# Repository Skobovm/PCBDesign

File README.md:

# PCBDesign
Re-learning how to use EAGLE, and various other circuits

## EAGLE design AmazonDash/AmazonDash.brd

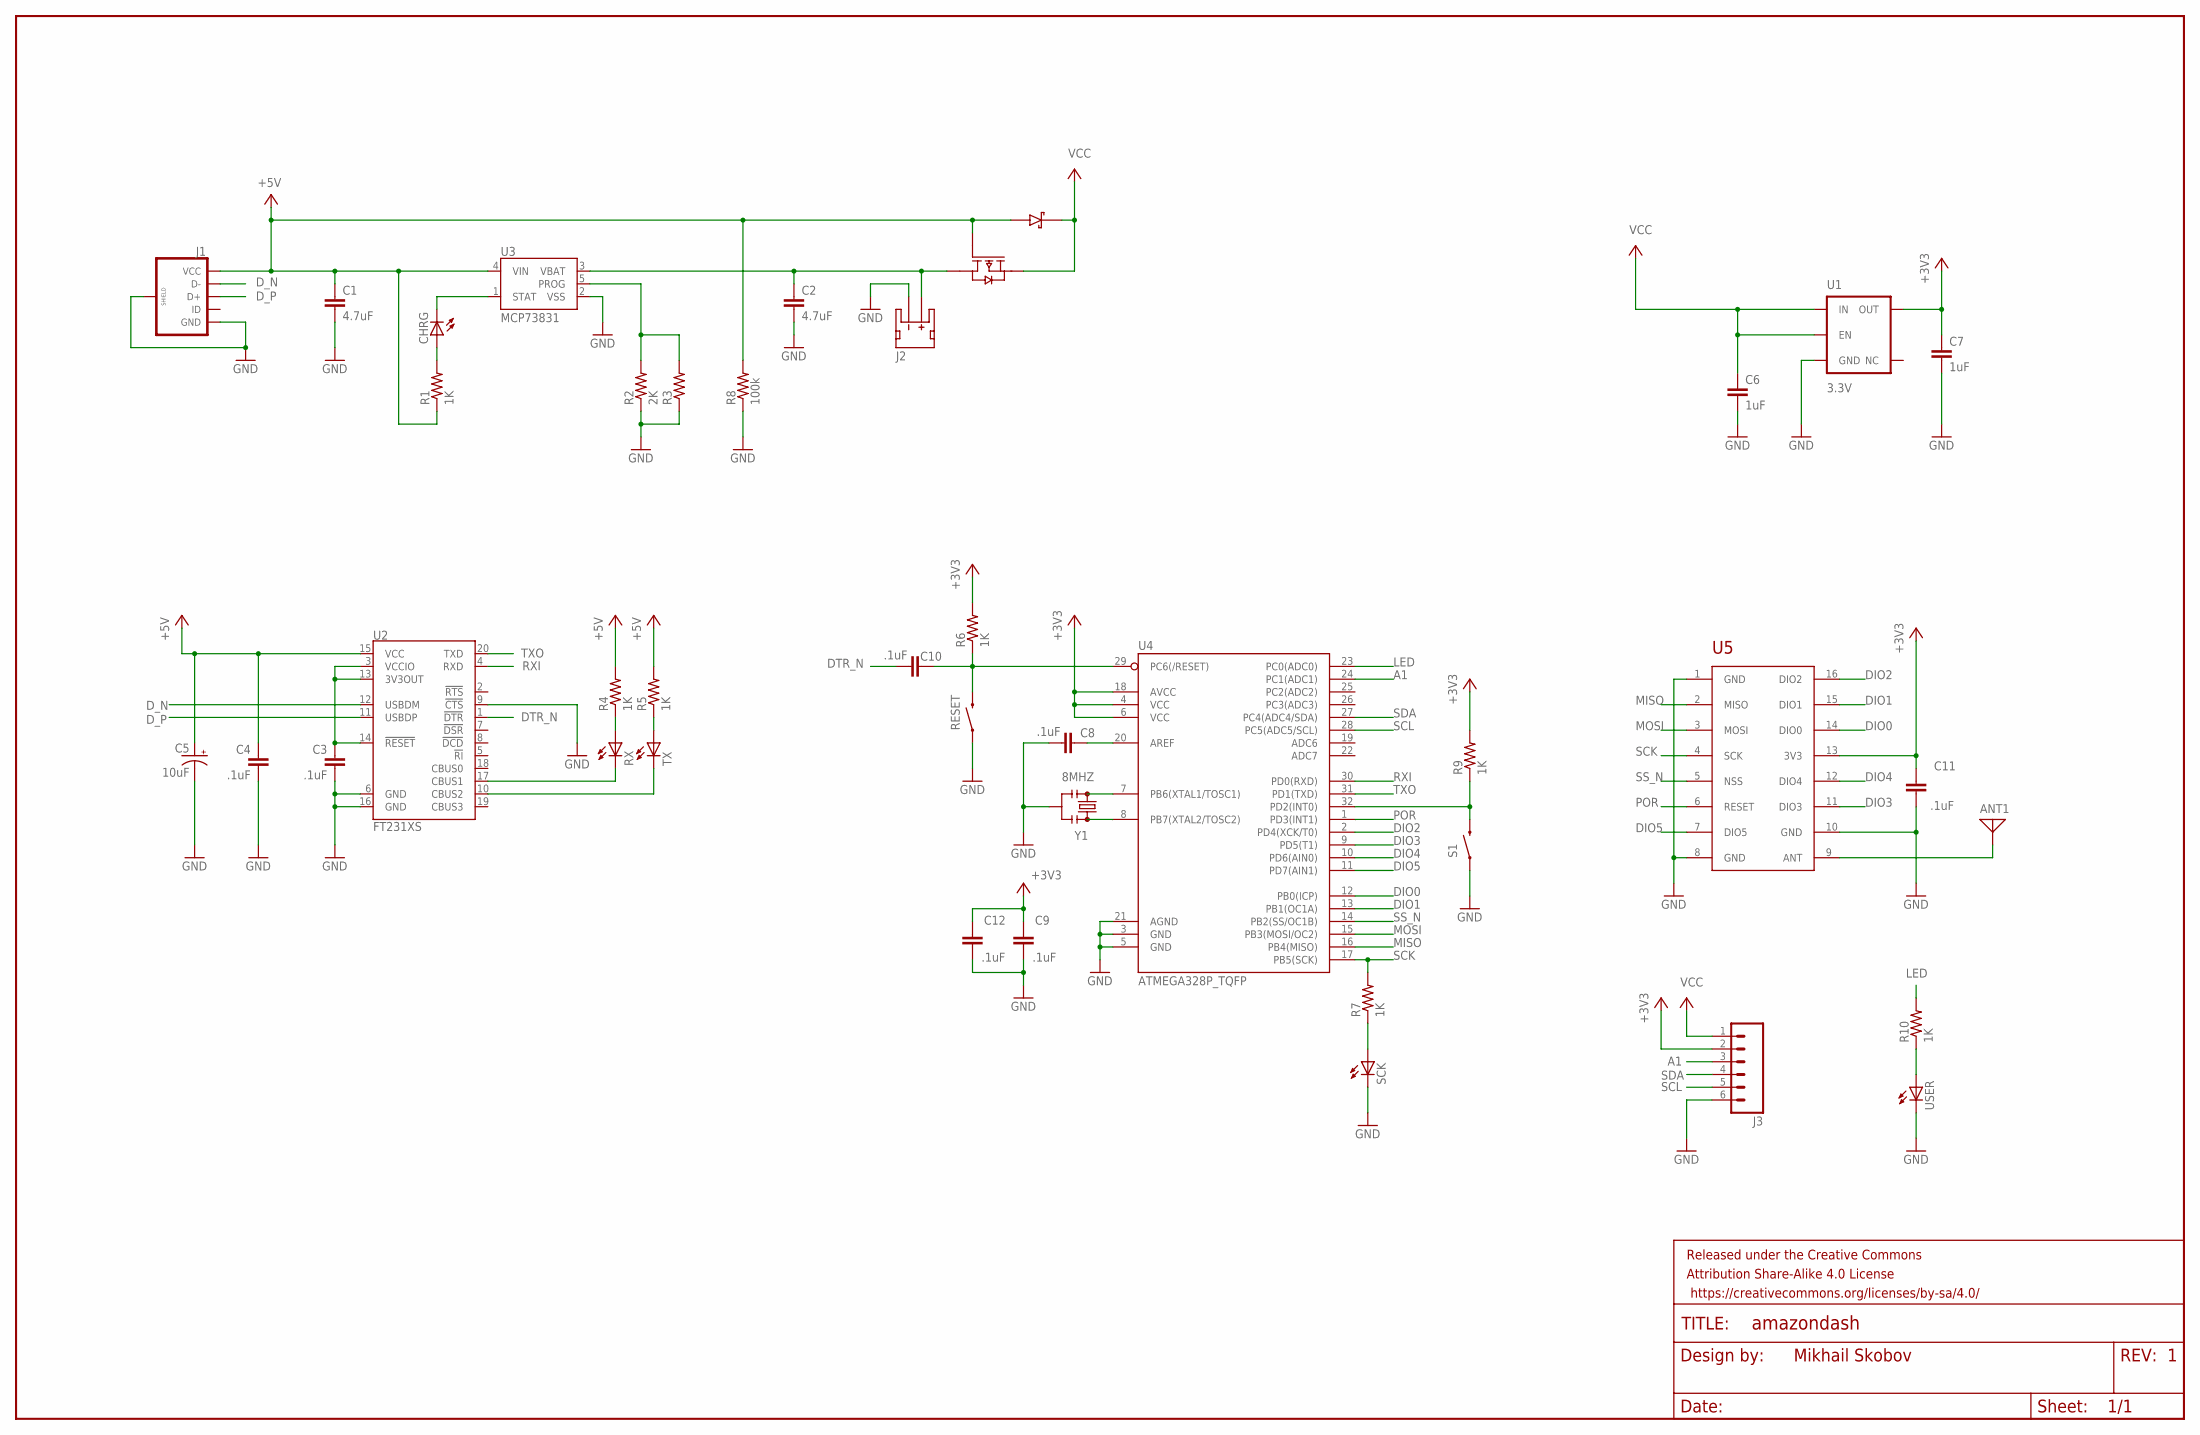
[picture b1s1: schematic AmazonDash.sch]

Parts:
ANT1: ANTENNA; PAD-01
C1, C2: 4.7uF; C0805
C3, C4, C8, C9, C10, C11, C12: .1uF; C0805
C5: 10uF; EIA3216
C6, C7: 1uF; C0805
CHRG: LEDCHIPLED_0805; CHIPLED_0805
FRAME2: FRAME-LEDGER; CREATIVE_COMMONS
J1: USB_MICROB_PLUGCONN-11752; USB-B-MICRO-SMD_V03
J2: JST_2MM_MALE; JST-2-SMD
J3: M06LOCK; 1X06_LOCK
R1, R4, R5, R6, R7, R9, R10: 1K; R0805
R2: 2K; R0805
R3: R-US_R0805; R0805
R8: 100k; R0805
RESET: SWITCH-MOMENTARY-2SMD; TACTILE-SWITCH-SMD
RX: LEDCHIPLED_0805; CHIPLED_0805
S1: SWITCH-MOMENTARY-2SMD; TACTILE-SWITCH-SMD
SCK: LEDCHIPLED_0805; CHIPLED_0805
TX: LEDCHIPLED_0805; CHIPLED_0805
U1: 3.3V; SOT23-5
U2: FT231XS; SSOP20_L
U3: MCP73831; SOT23-5
U4: ATMEGA328P_TQFP; TQFP32-08
U5: RFM69HCW; RFM69
U6: FDC6392S; SSOT-6
USER: LEDCHIPLED_0805; CHIPLED_0805
Y1: 8MHZ; RESONATOR-SMD

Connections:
+3V3: C7.1, C9.2, C11.2, C12.2, J3.2, R6.2, R9.2, U1.5 (OUT), U4.4 (VCC), U4.6 (VCC), U4.18 (AVCC), U5.13 (3V3)
+5V: C1.1, C4.1, C5.A (+), J1.VBUS (VCC), R1.1, R4.2, R5.2, R8.2, U2.15 (VCC), U3.4 (VIN), U6.1 (A), U6.3 (G)
A1: J3.3, U4.24 (PC1(ADC1))
DIO0: U4.12 (PB0(ICP)), U5.14 (DIO0)
DIO1: U4.13 (PB1(OC1A)), U5.15 (DIO1)
DIO2: U4.2 (PD4(XCK/T0)), U5.16 (DIO2)
DIO3: U4.9 (PD5(T1)), U5.11 (DIO3)
DIO4: U4.10 (PD6(AIN0)), U5.12 (DIO4)
DIO5: U4.11 (PD7(AIN1)), U5.7 (DIO5)
DTR_N: C10.1, U2.1 (!DTR)
D_N: J1.D-, U2.12 (USBDM)
D_P: J1.D+, U2.11 (USBDP)
GND: C1.2, C2.2, C3.2, C4.2, C5.C (-), C6.2, C7.2, C8.1, C9.1, C11.1, C12.1, J1.GND, J1.SHIELD1 (SHIELD), J1.SHIELD2 (SHIELD), J1.SHIELD3 (SHIELD), J2.1 (-), J3.6, R2.1, R3.1, R8.1, RESET.1, S1.1, SCK.C, U1.2 (GND), U2.6 (GND), U2.9 (!CTS), U2.16 (GND), U3.2 (VSS), U4.3 (GND), U4.5 (GND), U4.21 (AGND), U5.1 (GND), U5.8 (GND), U5.10 (GND), USER.C, Y1.2
LED: R10.2, U4.23 (PC0(ADC0))
MISO: U4.16 (PB4(MISO)), U5.2 (MISO)
MOSI: U4.15 (PB3(MOSI/OC2)), U5.3 (MOSI)
unnamed: RX.C, U2.17 (CBUS1)
unnamed: CHRG.C, U3.1 (STAT)
unnamed: CHRG.A, R1.2
unnamed: R4.1, RX.A
unnamed: R5.1, TX.A
unnamed: R2.2, R3.2, U3.5 (PROG)
unnamed: TX.C, U2.10 (CBUS2)
unnamed: C3.1, U2.3 (VCCIO), U2.13 (3V3OUT), U2.14 (!RESET)
unnamed: R9.1, S1.3 (2), U4.32 (PD2(INT0))
unnamed: R10.1, USER.A
unnamed: R7.1, SCK.A
unnamed: C10.2, R6.1, RESET.3 (2), U4.29 (PC6(/RESET))
unnamed: C8.2, U4.20 (AREF)
unnamed: U4.7 (PB6(XTAL1/TOSC1)), Y1.1
unnamed: U4.8 (PB7(XTAL2/TOSC2)), Y1.3
unnamed: ANT1.1, U5.9 (ANT)
POR: U4.1 (PD3(INT1)), U5.6 (RESET)
RXI: U2.4 (RXD), U4.30 (PD0(RXD))
SCK: R7.2, U4.17 (PB5(SCK)), U5.4 (SCK)
SCL: J3.5, U4.28 (PC5(ADC5/SCL))
SDA: J3.4, U4.27 (PC4(ADC4/SDA))
SS_N: U4.14 (PB2(SS/OC1B)), U5.5 (NSS)
TXO: U2.20 (TXD), U4.31 (PD1(TXD))
VBAT: C2.1, J2.2 (+), U3.3 (VBAT), U6.4 (S)
VCC: C6.1, J3.1, U1.1 (IN), U1.3 (EN), U6.2 (D), U6.6 (C)

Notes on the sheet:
Mikhail Skobov

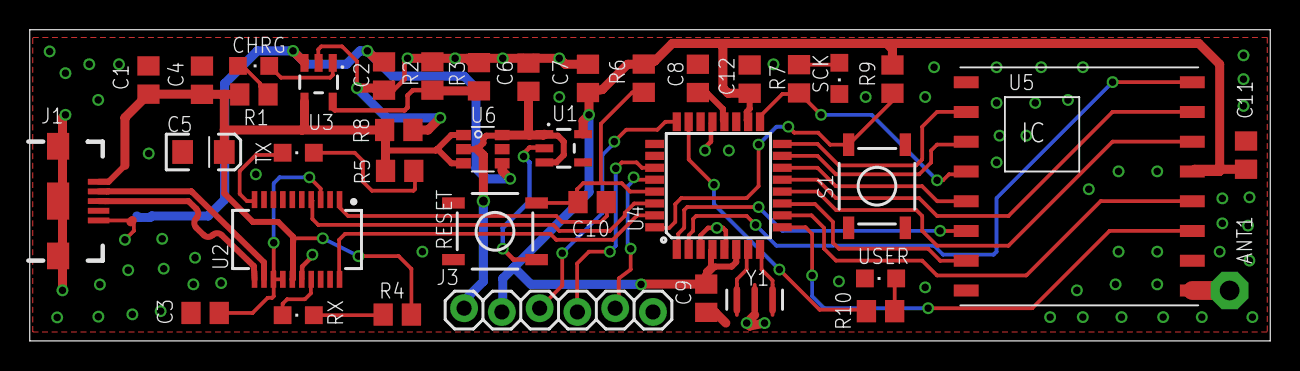
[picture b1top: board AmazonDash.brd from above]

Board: 2 copper layers, 83.4 x 20.9 mm, 41 parts (1 on the bottom side), 41 nets.

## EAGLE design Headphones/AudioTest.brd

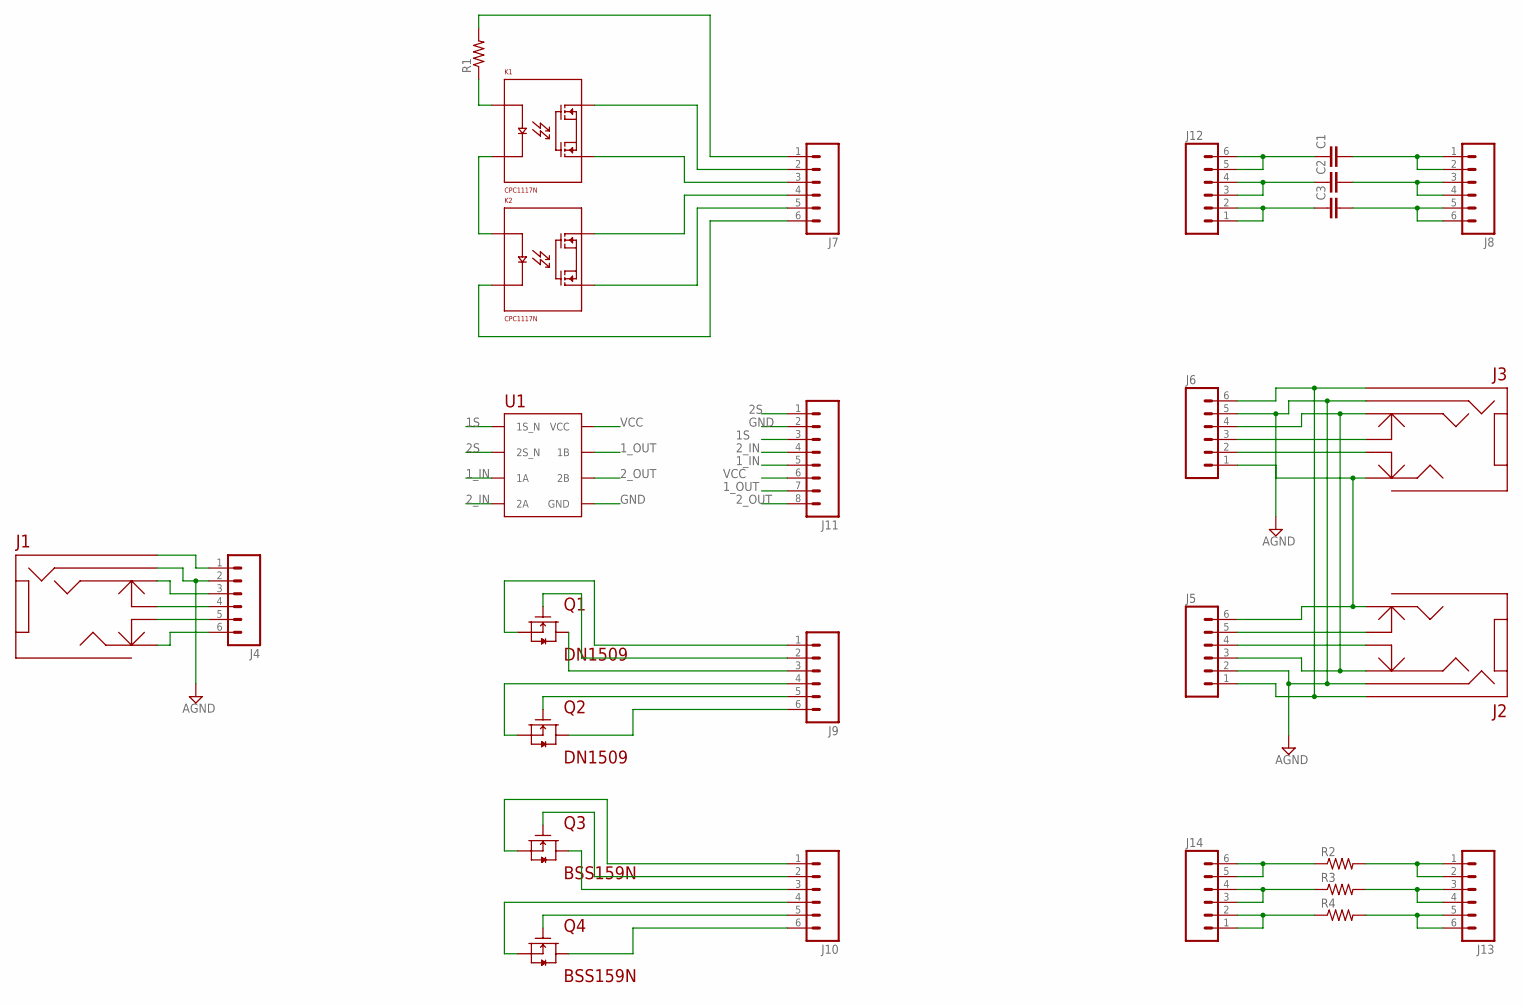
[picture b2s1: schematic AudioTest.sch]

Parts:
C1, C2, C3: C-EUC1210; C1210
J1, J2, J3: SJ-43516; SJ-43516-SMT
J4, J5, J6, J7, J8, J9, J10, J12, J13, J14: M06LOCK; 1X06_LOCK
J11: M08LOCK; 1X08_LOCK
K1, K2: CPC1117N; 4-SOP
Q1, Q2: DN1509; SOT-23-5
Q3, Q4: BSS159N; SOT-23-3
R1: R-US_R0805; R0805
R2, R3, R4: R-US_M0805; M0805
U1: FSA553; 9-UFBGA-NSMD

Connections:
1S: J11.3, U1.C1 (1S_N)
1_IN: J11.5, U1.A1 (1A)
1_L: J1.2 (LEFT), J4.6
1_L_SW: J1.5 (LEFT_NC), J4.5
1_M: J1.1 (MIC), J4.1
1_OUT: J11.7, U1.A3 (1B)
1_R: J1.3 (RIGHT), J4.3
1_R_SW: J1.6 (RIGHT_NC), J4.4
2S: J11.1, U1.C3 (2S_N)
2_IN: J11.4, U1.B1 (2A)
2_L: J2.2 (LEFT), J3.2 (LEFT), J5.6, J6.1
2_L_SW: J2.5 (LEFT_NC), J5.5
2_M: J2.1 (MIC), J3.1 (MIC), J5.1, J6.6
2_OUT: J11.8, U1.B3 (2B)
2_R: J2.3 (RIGHT), J3.3 (RIGHT), J5.3, J6.4
2_R_SW: J2.6 (RIGHT_NC), J5.4
3_SW_L: J3.5 (LEFT_NC), J6.2
3_SW_R: J3.6 (RIGHT_NC), J6.3
AGND: J1.4 (GND), J2.4 (GND), J3.4 (GND), J4.2, J5.2, J6.5
D1: J9.3, Q1.2 (D)
D2: J9.6, Q2.2 (D)
D3: J10.3, Q3.3 (D)
D4: J10.6, Q4.3 (D)
G1: J9.2, Q1.5 (G)
G2: J9.5, Q2.5 (G)
G3: J10.2, Q3.1 (G)
G4: J10.5, Q4.1 (G)
GND: J11.2, U1.C2 (GND)
unnamed: C3.1, J12.1, J12.2
unnamed: C3.2, J8.5, J8.6
unnamed: K1.1 (A), R1.1
unnamed: K1.2 (C), K2.1 (A)
unnamed: C2.2, J8.3, J8.4
unnamed: C1.2, J8.1, J8.2
unnamed: C1.1, J12.5, J12.6
unnamed: C2.1, J12.3, J12.4
unnamed: J14.1, J14.2, R4.1
unnamed: J13.5, J13.6, R4.2
unnamed: J13.3, J13.4, R3.2
unnamed: J13.1, J13.2, R2.2
unnamed: J14.5, J14.6, R2.1
unnamed: J14.3, J14.4, R3.1
R_GND: J7.6, K2.2 (C)
R_IN1: J7.2, K1.4 (LOAD1)
R_IN2: J7.4, K2.4 (LOAD1)
R_OUT1: J7.3, K1.3 (LOAD2)
R_OUT2: J7.5, K2.3 (LOAD2)
R_V+: J7.1, R1.2
S1: J9.1, Q1.4 (S)
S2: J9.4, Q2.4 (S)
S3: J10.1, Q3.2 (S)
S4: J10.4, Q4.2 (S)
VCC: J11.6, U1.A2 (VCC)

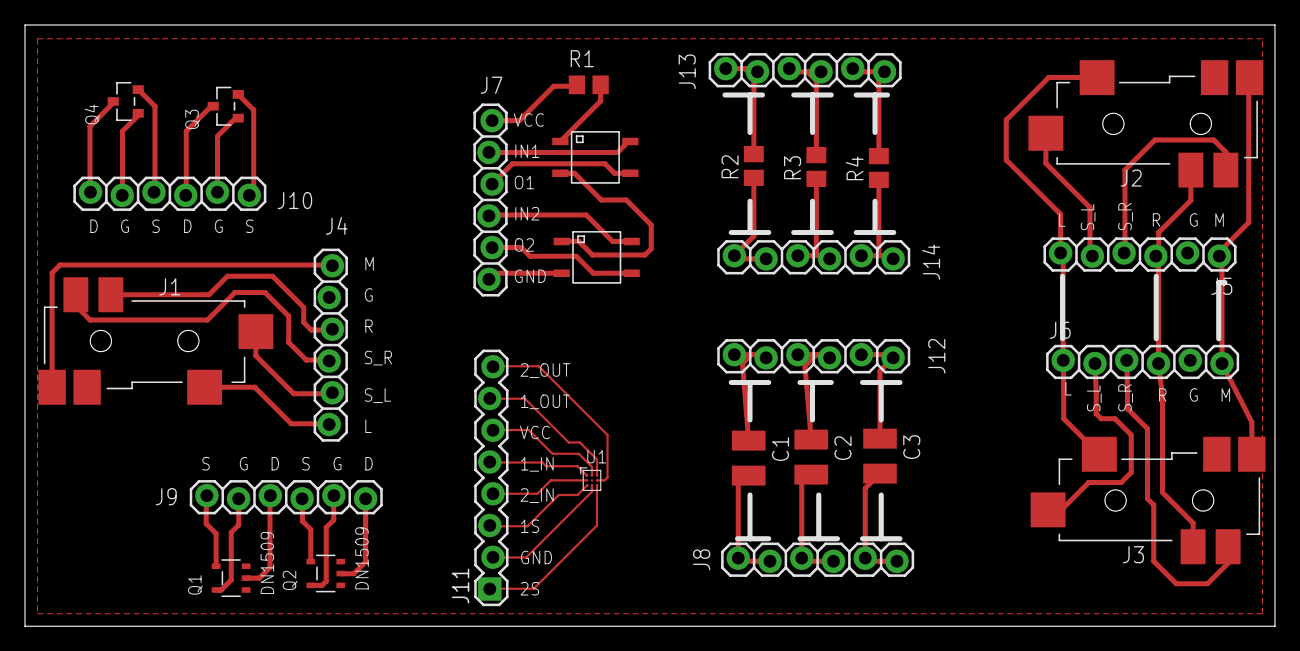
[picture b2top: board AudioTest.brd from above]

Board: 2 copper layers, 100.0 x 48.1 mm, 28 parts (0 on the bottom side), 53 nets.

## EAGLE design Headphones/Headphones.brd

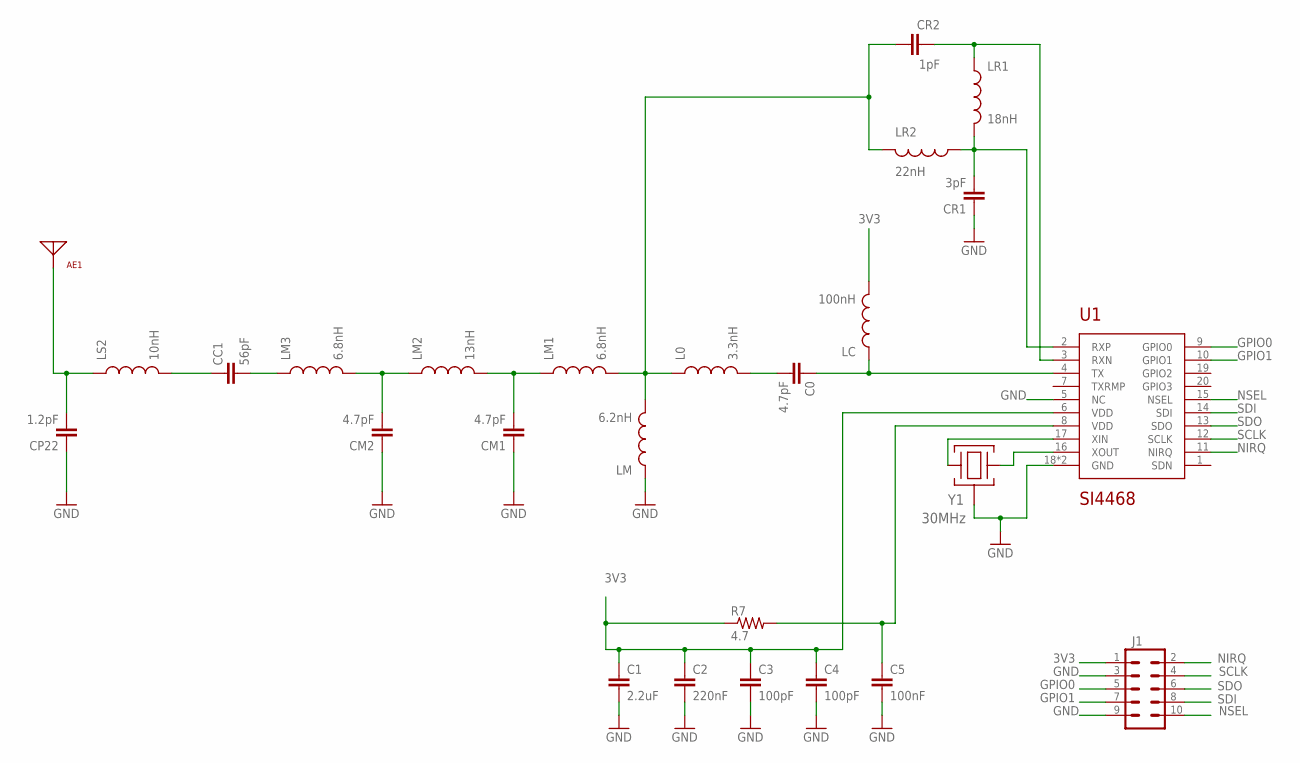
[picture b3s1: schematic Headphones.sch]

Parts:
AE1: ANT1204LL05R0915A; ANT-1204
C0: 4.7pF; C0603
C1: 2.2uF; C0603
C2: 220nF; C0603
C3, C4: 100pF; C0603
C5: 100nF; C0603
CC1: 56pF; C0603
CM1, CM2: 4.7pF; C0603
CP22: 1.2pF; C0603
CR1: 3pF; C0603
CR2: 1pF; C0603
J1: M05X2PTH; AVR_ICSP
L0: 3.3nH; 0603
LC: 100nH; 0603
LM: 6.2nH; 0603
LM1, LM3: 6.8nH; 0603
LM2: 13nH; 0603
LR1: 18nH; 0603
LR2: 22nH; 0603
LS2: 10nH; 0603
R7: 4.7; R0603
U1: SI4468; QFN20-SI
Y1: 30MHz; ABM10

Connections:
3V3: C1.1, C2.1, C3.1, C4.1, J1.1, LC.2, R7.1, U1.6 (VDD)
GND: C1.2, C2.2, C3.2, C4.2, C5.2, CM1.1, CM2.1, CP22.1, CR1.1, J1.3, J1.9, LM.1, U1.5 (NC), U1.18 (GND), U1.21 (GND), Y1.2 (GND), Y1.4 (GND)
GPIO0: J1.5, U1.9 (GPIO0)
GPIO1: J1.7, U1.10 (GPIO1)
unnamed: U1.16 (XOUT), Y1.1
unnamed: U1.17 (XIN), Y1.3 (2)
unnamed: C0.2, L0.2
unnamed: CR2.2, LR1.1, U1.3 (RXN)
unnamed: CR1.2, LR1.2, LR2.1, U1.2 (RXP)
unnamed: CR2.1, L0.1, LM.2, LM1.2, LR2.2
unnamed: C5.1, R7.2, U1.8 (VDD)
unnamed: CC1.2, LM3.1
unnamed: CC1.1, LS2.2
unnamed: C0.1, LC.1, U1.4 (TX)
unnamed: CM1.2, LM1.1, LM2.2
unnamed: CM2.2, LM2.1, LM3.2
unnamed: AE1.1, CP22.2, LS2.1
NIRQ: J1.2, U1.11 (NIRQ)
NSEL: J1.10, U1.15 (NSEL)
SCLK: J1.4, U1.12 (SCLK)
SDI: J1.8, U1.14 (SDI)
SDO: J1.6, U1.13 (SDO)

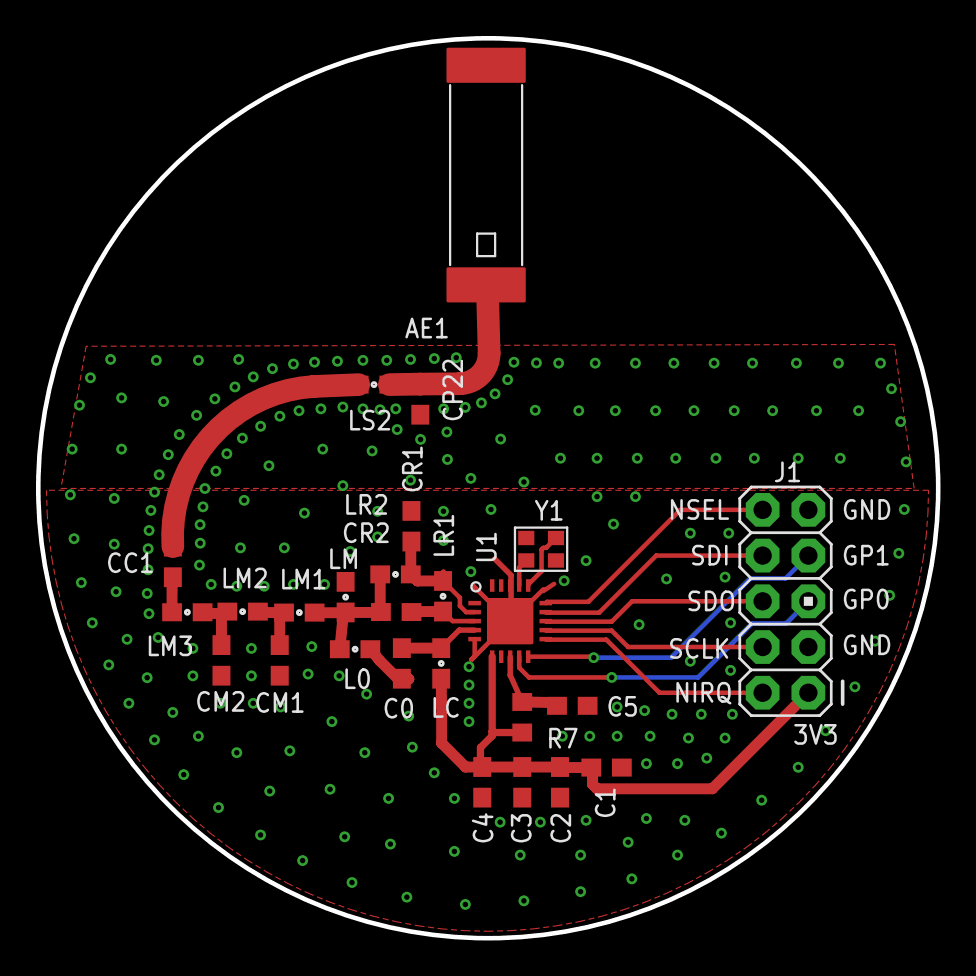
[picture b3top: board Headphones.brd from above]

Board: 2 copper layers, 50.0 x 50.0 mm, 26 parts (0 on the bottom side), 22 nets.

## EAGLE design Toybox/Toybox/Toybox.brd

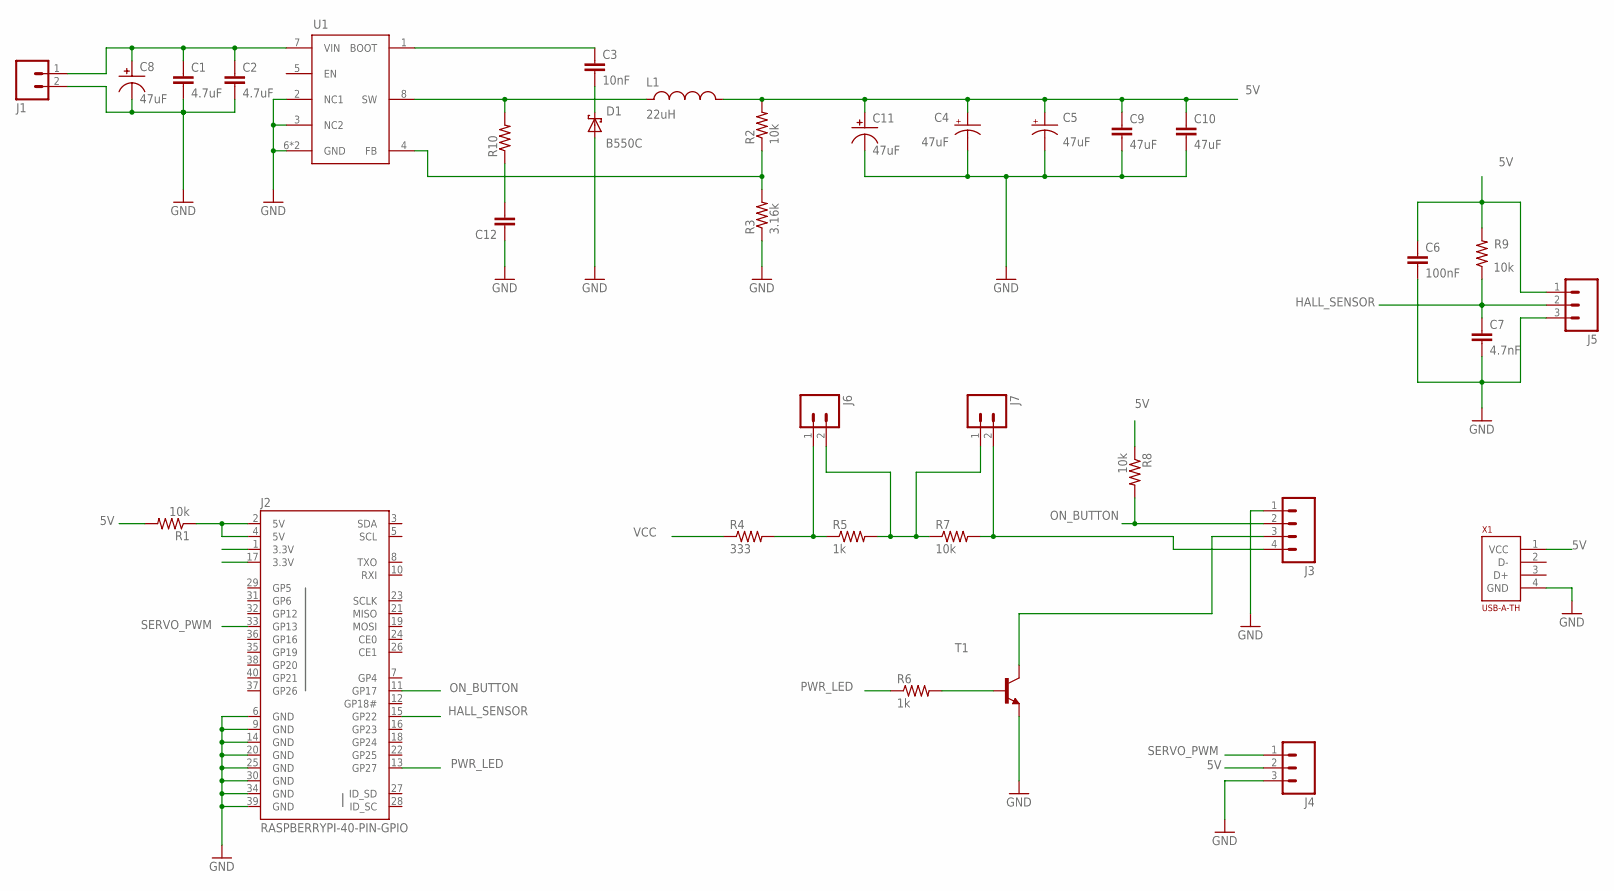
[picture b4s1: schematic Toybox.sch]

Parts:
C1, C2: 4.7uF; C0805
C3: 10nF; C0805
C4, C5: 47uF; T/3528-12R
C6: 100nF; C0805
C7: 4.7nF; C0805
C8, C11: 47uF; CPOL-RADIAL-6.3
C9, C10: 47uF; 1210
C12: C-EUC0805; C0805
D1: B550C; SMC
J1: M025MM; SCREWTERMINAL-5MM-2
J2: RASPBERRYPI-40-PIN-GPIO; 2X20-SHROUDED
J3: M041X04_NO_SILK; 1X04_NO_SILK
J4, J5: M03PTH; 1X03
J6, J7: M02PTH; 1X02
L1: 22uH; IND-SRR1210
R1, R2, R7, R8, R9: 10k; R0805
R3: 3.16k; R0805
R4: 333; R0805
R5, R6: 1k; R0805
R10: R-US_R0805; R0805
T1: MMBT2222ALT1-NPN-SOT23-BEC; SOT23-BEC
U1: RT8289; RT8289-SOP-8
X1: USB-A-TH

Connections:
5V: C4.+, C5.+, C6.1, C9.1, C10.1, C11.1, J4.2, J5.1, L1.P$2, R1.2, R2.2, R8.1, R9.2, X1.1 (VCC)
GND: C1.2, C2.2, C4.-, C5.-, C6.2, C7.2, C8.2, C9.2, C10.2, C11.2, C12.1, D1.A, J1.2, J2.6 (GND), J2.9 (GND), J2.14 (GND), J2.20 (GND), J2.25 (GND), J2.30 (GND), J2.34 (GND), J2.39 (GND), J3.1, J4.3, J5.3, R3.1, T1.E, U1.2 (NC1), U1.3 (NC2), U1.6 (GND), U1.9 (GND), X1.4 (GND)
HALL_SENSOR: C7.1, J2.15 (GP22), J5.2, R9.1
unnamed: J3.3, T1.C
unnamed: J2.2 (5V), J2.4 (5V), R1.1
unnamed: R2.1, R3.2, U1.4 (FB)
unnamed: R6.2, T1.B
unnamed: C3.2, D1.C
unnamed: C3.1, U1.1 (BOOT)
unnamed: J6.1, R4.2, R5.1
unnamed: J6.2, J7.1, R5.2, R7.1
unnamed: J3.4, J7.2, R7.2
unnamed: C12.2, R10.1
NC1: J2.1 (3.3V)
NC2: J2.17 (3.3V)
ON_BUTTON: J2.11 (GP17), J3.2, R8.2
PWR_LED: J2.13 (GP27), R6.1
SERVO_PWM: J2.33 (GP13), J4.1
SW: L1.P$1, R10.2, U1.8 (SW)
VCC: C1.1, C2.1, C8.1, J1.1, R4.1, U1.7 (VIN)

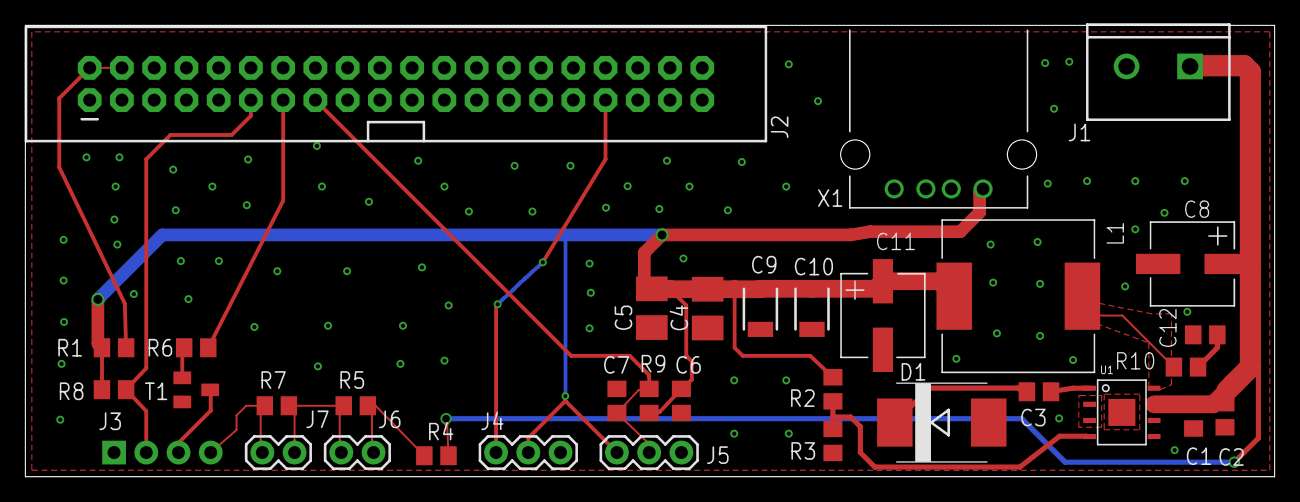
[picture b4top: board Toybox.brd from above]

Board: 2 copper layers, 98.4 x 35.6 mm, 34 parts (0 on the bottom side), 18 nets.

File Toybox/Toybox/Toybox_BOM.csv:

"Part";"Value";"Device";"Package";"Description";"PROD_ID";"STOREFRONT_ID";
"C1";"4.7uF";"C-EUC0805";"C0805";"CAPACITOR, European symbol";"";"";
"C2";"4.7uF";"C-EUC0805";"C0805";"CAPACITOR, European symbol";"";"";
"C3";"10nF";"C-EUC0603";"C0603";"CAPACITOR, European symbol";"";"";
"C4";"47uF";"CPOL-USB/3528-21R";"T/3528-12R";"POLARIZED CAPACITOR, American symbol";"";"";
"C5";"47uF";"CPOL-USB/3528-21R";"T/3528-12R";"POLARIZED CAPACITOR, American symbol";"";"";
"C6";"100nF";"C-EUC0603";"C0603";"CAPACITOR, European symbol";"";"";
"C7";"4.7nF";"C-EUC0603";"C0603";"CAPACITOR, European symbol";"";"";
"D1";"B550C";"SCHOTTKY-DIODESMC";"SMC";"Schottky Diode";"";"";
"J1";"";"M025MM";"SCREWTERMINAL-5MM-2";"Standard 2-pin 0.1" header. Use with";"";"PRT-08432";
"J2";"RASPBERRYPI-40-PIN-GPIO";"RASPBERRYPI-40-PIN-GPIO";"2X20-SHROUDED";"Second Generation Raspberry Pi GPIO Header";"";"";
"J3";"";"M04PTH";"1X04";"Header 4";"CONN-09696";"";
"J4";"";"M03PTH";"1X03";"Header 3";"";"";
"J5";"";"M03PTH";"1X03";"Header 3";"";"";
"JP1";"";"JP1Q";"JP1";"JUMPER";"";"";
"JP2";"";"JP1Q";"JP1";"JUMPER";"";"";
"L1";"10uH";"SRN1060";"SRN1060";"SRN1060 - Semi-shielded power inductor";"";"";
"R1";"10k";"R-US_R0603";"R0603";"RESISTOR, American symbol";"";"";
"R2";"10k";"R-US_R0603";"R0603";"RESISTOR, American symbol";"";"";
"R3";"3.16k";"R-US_R0603";"R0603";"RESISTOR, American symbol";"";"";
"R4";"333";"R-US_R0603";"R0603";"RESISTOR, American symbol";"";"";
"R5";"1k";"R-US_R0603";"R0603";"RESISTOR, American symbol";"";"";
"R6";"1k";"R-US_R0603";"R0603";"RESISTOR, American symbol";"";"";
"R7";"10k";"R-US_R0603";"R0603";"RESISTOR, American symbol";"";"";
"R8";"10k";"R-US_R0603";"R0603";"RESISTOR, American symbol";"";"";
"R9";"10k";"R-US_R0603";"R0603";"RESISTOR, American symbol";"";"";
"T1";"";"MMBT2222ALT1-NPN-SOT23-BEC";"SOT23-BEC";"NPN Transistror";"";"";
"U1";"";"RT8289";"RT8289-SOP-8";"RT8289GSP - Step-Down Regulator "Buck Converter"";"";"";
"X1";"USB-A-TH";"USB-A-TH";"USB-A-TH";"USB Type A Female Connector";"";"";

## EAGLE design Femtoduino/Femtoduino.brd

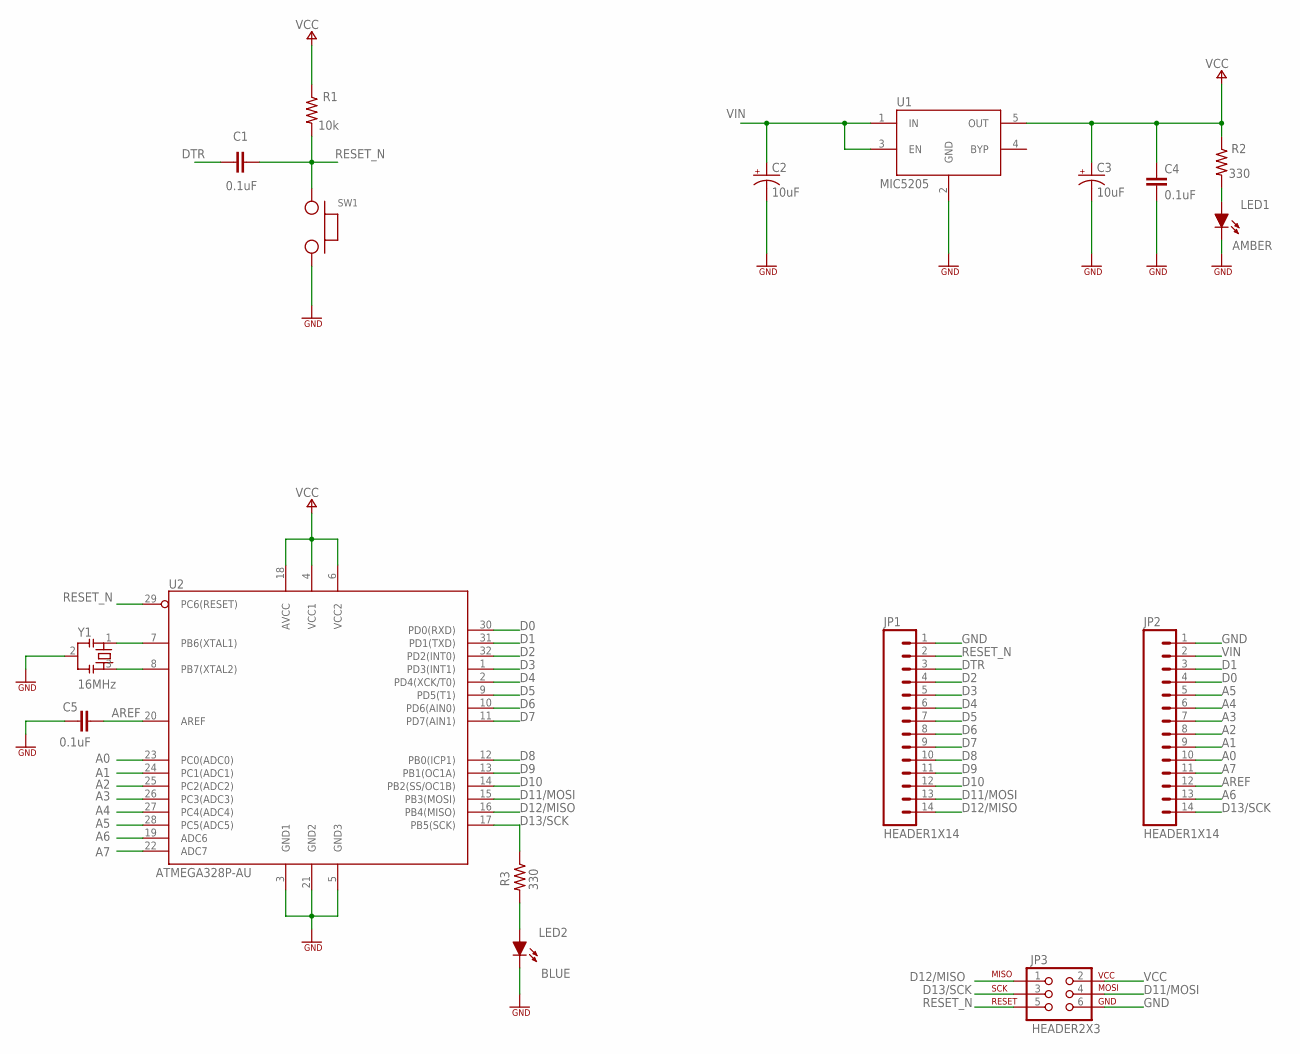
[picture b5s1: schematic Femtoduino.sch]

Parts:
C1, C4, C5: 0.1uF; SMD0603
C2, C3: 10uF; EIA3216
JP1, JP2: HEADER1X14; 1X14
JP3: HEADER2X3; 2X3
LED1: AMBER; LED_0805
LED2: BLUE; LED_0805
R1: 10k; SMD0603
R2, R3: 330; SMD0603
SW1: SWITCH; SWITCH-SPST
U1: MIC5205; SOT23-5
U2: ATMEGA328P-AU; TQFP32
Y1: 16MHz; CSTCE

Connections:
A0: JP2.10, U2.23 (PC0(ADC0))
A1: JP2.9, U2.24 (PC1(ADC1))
A2: JP2.8, U2.25 (PC2(ADC2))
A3: JP2.7, U2.26 (PC3(ADC3))
A4: JP2.6, U2.27 (PC4(ADC4))
A5: JP2.5, U2.28 (PC5(ADC5))
A6: JP2.13, U2.19 (ADC6)
A7: JP2.11, U2.22 (ADC7)
AREF: C5.2, JP2.12, U2.20 (AREF)
D0: JP2.4, U2.30 (PD0(RXD))
D1: JP2.3, U2.31 (PD1(TXD))
D2: JP1.4, U2.32 (PD2(INT0))
D3: JP1.5, U2.1 (PD3(INT1))
D4: JP1.6, U2.2 (PD4(XCK/T0))
D5: JP1.7, U2.9 (PD5(T1))
D6: JP1.8, U2.10 (PD6(AIN0))
D7: JP1.9, U2.11 (PD7(AIN1))
D8: JP1.10, U2.12 (PB0(ICP1))
D9: JP1.11, U2.13 (PB1(OC1A))
D10: JP1.12, U2.14 (PB2(SS/OC1B))
D11/MOSI: JP1.13, JP3.4, U2.15 (PB3(MOSI))
D12/MISO: JP1.14, JP3.1, U2.16 (PB4(MISO))
D13/SCK: JP2.14, JP3.3, R3.1, U2.17 (PB5(SCK))
DTR: C1.1, JP1.3
GND: C2.C (-), C3.C (-), C4.2, C5.1, JP1.1, JP2.1, JP3.6, LED1.C, LED2.C, SW1.2, U1.2 (GND), U2.3 (GND1), U2.5 (GND3), U2.21 (GND2), Y1.2
unnamed: LED2.A, R3.2
unnamed: LED1.A, R2.2
unnamed: U2.7 (PB6(XTAL1)), Y1.1
unnamed: U2.8 (PB7(XTAL2)), Y1.3
RESET_N: C1.2, JP1.2, JP3.5, R1.2, SW1.1, U2.29 (PC6(RESET))
VCC: C3.A (+), C4.1, JP3.2, R1.1, R2.1, U1.5 (OUT), U2.4 (VCC1), U2.6 (VCC2), U2.18 (AVCC)
VIN: C2.A (+), JP2.2, U1.1 (IN), U1.3 (EN)

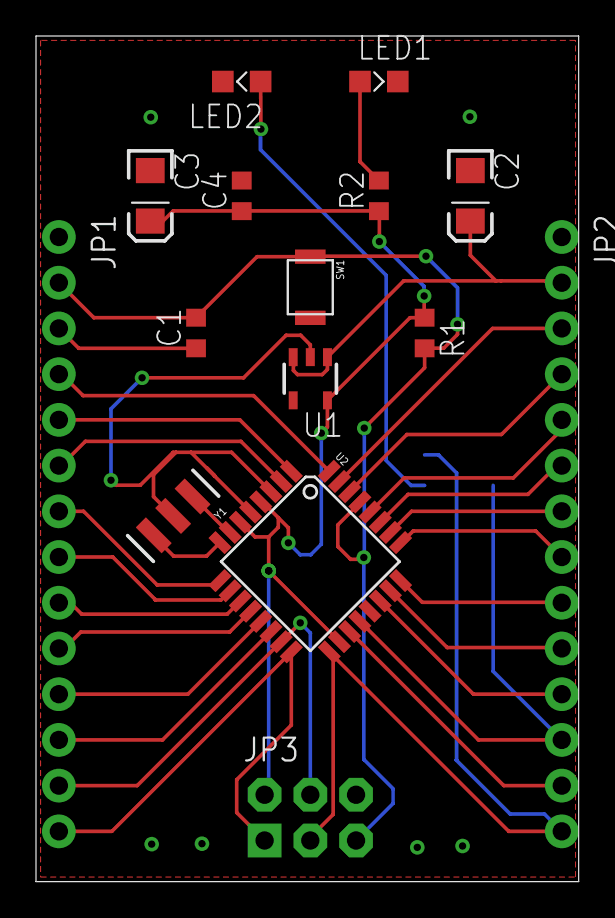
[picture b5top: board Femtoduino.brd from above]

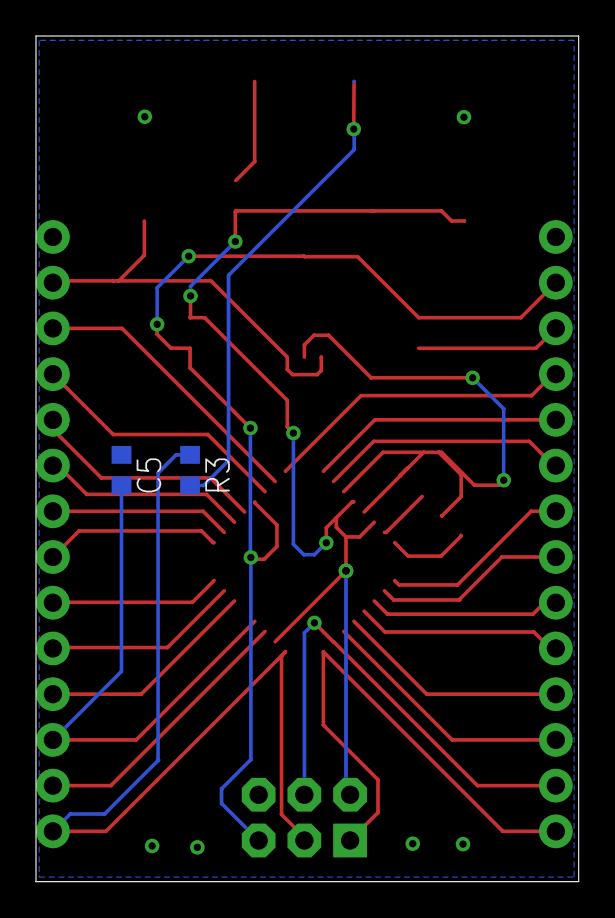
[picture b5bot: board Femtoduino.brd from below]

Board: 2 copper layers, 30.1 x 47.0 mm, 17 parts (2 on the bottom side), 32 nets.

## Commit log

2016-10-17 The femtoduino circuit is complete. The components have been laid out on the board. Need to route still
2016-10-17 Finished the routing and fill for the board
2016-10-19 Adding a modified file
2016-10-21 Added the RT8289 step down converter to the library
2016-10-24 Adding the USB symbol and layout. Still need to connect device pins
2016-10-24 Started the schematic
2016-10-26 Beginning the hall effect module
2016-10-26 Circuit is mostly done. Just need to add the power supply terminal
2016-10-27 Layout is mostly complete. Need to wire small components and ground planes
2016-10-27 Circuit is complete. Add logo if there is time
2016-10-28 Removing the ignored files. Started personal DRU and CAM folder. Created BOM
2016-11-14 Created the Yageo antenna and the rf transciever si4468
2016-11-14 Saving work
2016-11-15 Component placement is mostly complete. Need to finish routing
2016-11-16 Finished most of the layout. Still need to run DRC, ERC, and standardize text
2016-11-16 Added a bunch of vias everywhere
2016-11-17 Fixed antenna and transciever stop masks. Finished via placement. DRC checks out
2016-11-17 Minor routing changes to antenna
2016-11-17 More fixes
2016-11-17 Removing gerbers
2016-11-18 Fixed up the toybox board. Added different passive components all around
2016-12-03 Moved jumper pin names to tNames layer
2017-01-07 not sure what this is
2017-01-17 Finished Amazon Dash button layout. Started headphone test board design
2017-01-17 Started audio testing schematic
2017-01-17 Created components and completed most of audio test schematic
2017-02-06 Adding Amazon Dash CAM files and added outline to schematic
2017-02-10 Added the STM32l476 device
2017-02-15 Added some stuff to the library
2017-02-20 Created several components for headphones
2017-02-21 Created solder bridge and some modifications
2017-02-26 Added microphone device. Pretty crappy footprint causes many errors

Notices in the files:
parts and their libraries:
SparkFun-Capacitors: Licensing: Creative Commons ShareAlike 4.0 International - https://creativecommons.org/licenses/by-sa/4.0
SparkFun-Aesthetics: Released under the Creative Commons Attribution Share-Alike 4.0 License
SparkFun-Aesthetics: https://creativecommons.org/licenses/by-sa/4.0
